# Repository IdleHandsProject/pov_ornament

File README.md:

# Persistence of Vision Christmas Ornament
A Persistence of Vision Christmas Ornament 

## Check out the video! - Click the Image

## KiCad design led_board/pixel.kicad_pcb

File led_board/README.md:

# ESPEverywhere
ESP8266 Special Make/100 Kickstarter Edition

Check out why this board exists here:
https://www.youtube.com/watch?v=67Kh_ikb-ds

The ESP Everywhere was made to take part in the Kickstarter Make/100 Campaign
You can get 1 of 100 boards assembled by me. Or you can Make your own.
Kickstarter is here:
https://www.kickstarter.com/projects/idlehandsdev/esp-everywhere-kickstarter-special-make-100

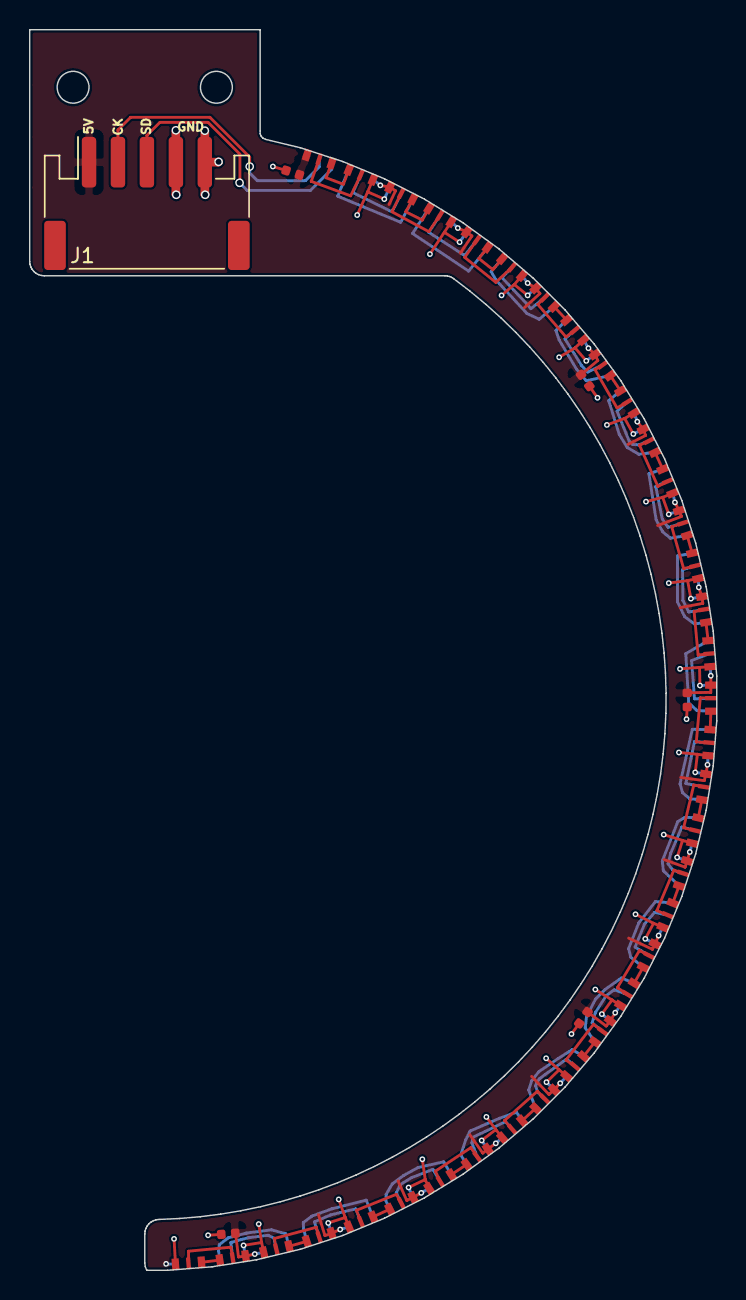
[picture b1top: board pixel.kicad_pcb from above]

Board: 2 copper layers, 47.5 x 85.7 mm, 42 parts (0 on the bottom side), 74 nets.

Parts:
C1, C10: e; C_0402_1005Metric
C3, C6, C7: 10uF; C_0402_1005Metric
J1: LED_Conn; JST_PH_S5B-PH-SM4-TB_1x05-1MP_P2.00mm_Horizontal
U1, U3, U5, U7, U9, U11, U13, U15, U17, U19, U21, U23, U25, U27, U29, U31, U33, U35: APA102; LED-APA102-2020_Edge
U2, U4, U6, U8, U10, U12, U14, U16, U18, U20, U22, U24, U26, U28, U30, U32, U34, U36: APA102; LED-APA102-2020_Edge_R

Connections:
+5V: C1.1, C3.1, C6.1, C7.1, C10.1, J1.1, U1.1, U2.1, U3.1, U4.1, U5.1, U6.1, U7.1, U8.1, U9.1, U10.1, U11.1, U12.1, U13.1, U14.1, U15.1, U16.1, U17.1, U18.1, U19.1, U20.1, U21.1, U22.1, U23.1, U24.1, U25.1, U26.1, U27.1, U28.1, U29.1, U30.1, U31.1, U32.1, U33.1, U34.1, U35.1, U36.1
CK1: U16.2, U17.5
CK2: U32.2, U33.5
CKS: J1.2, U1.5
GND: C1.2, C3.2, C6.2, C7.2, C10.2, J1.4, J1.5, U1.6, U2.6, U3.6, U4.6, U5.6, U6.6, U7.6, U8.6, U9.6, U10.6, U11.6, U12.6, U13.6, U14.6, U15.6, U16.6, U17.6, U18.6, U19.6, U20.6, U21.6, U22.6, U23.6, U24.6, U25.6, U26.6, U27.6, U28.6, U29.6, U30.6, U31.6, U32.6, U33.6, U34.6, U35.6, U36.6
unnamed: U1.2, U2.5
unnamed: U1.3, U2.4
unnamed: U2.2, U3.5
unnamed: U2.3, U3.4
unnamed: U3.2, U4.5
unnamed: U3.3, U4.4
unnamed: U4.2, U5.5
unnamed: U4.3, U5.4
unnamed: U5.2, U6.5
unnamed: U5.3, U6.4
unnamed: U6.2, U7.5
unnamed: U6.3, U7.4
unnamed: U7.2, U8.5
unnamed: U7.3, U8.4
unnamed: U8.2, U9.5
unnamed: U8.3, U9.4
unnamed: U10.2, U11.5
unnamed: U10.3, U11.4
unnamed: U9.3, U10.4
unnamed: U9.2, U10.5
unnamed: U11.2, U12.5
unnamed: U11.3, U12.4
unnamed: U12.2, U13.5
unnamed: U12.3, U13.4
unnamed: U13.2, U14.5
unnamed: U13.3, U14.4
unnamed: U14.2, U15.5
unnamed: U14.3, U15.4
unnamed: U15.2, U16.5
unnamed: U15.3, U16.4
unnamed: U17.2, U18.5
unnamed: U17.3, U18.4
unnamed: U18.2, U19.5
unnamed: U18.3, U19.4
unnamed: U19.2, U20.5
unnamed: U19.3, U20.4
unnamed: U20.2, U21.5
unnamed: U20.3, U21.4
unnamed: U21.2, U22.5
unnamed: U21.3, U22.4
unnamed: U22.2, U23.5
unnamed: U22.3, U23.4
unnamed: U23.2, U24.5
unnamed: U23.3, U24.4
unnamed: U24.2, U25.5
unnamed: U24.3, U25.4
unnamed: U25.2, U26.5
unnamed: U25.3, U26.4
unnamed: U26.2, U27.5
unnamed: U26.3, U27.4
unnamed: U27.2, U28.5
unnamed: U27.3, U28.4
unnamed: U28.2, U29.5
unnamed: U28.3, U29.4
unnamed: U29.2, U30.5
unnamed: U29.3, U30.4
unnamed: U30.2, U31.5
unnamed: U30.3, U31.4
unnamed: U31.2, U32.5
unnamed: U31.3, U32.4
unnamed: U33.2, U34.5
unnamed: U33.3, U34.4
unnamed: U34.2, U35.5
unnamed: U34.3, U35.4
unnamed: U35.2, U36.5
unnamed: U35.3, U36.4
SD1: U16.3, U17.4
SD2: U32.3, U33.4
SDS: J1.3, U1.4

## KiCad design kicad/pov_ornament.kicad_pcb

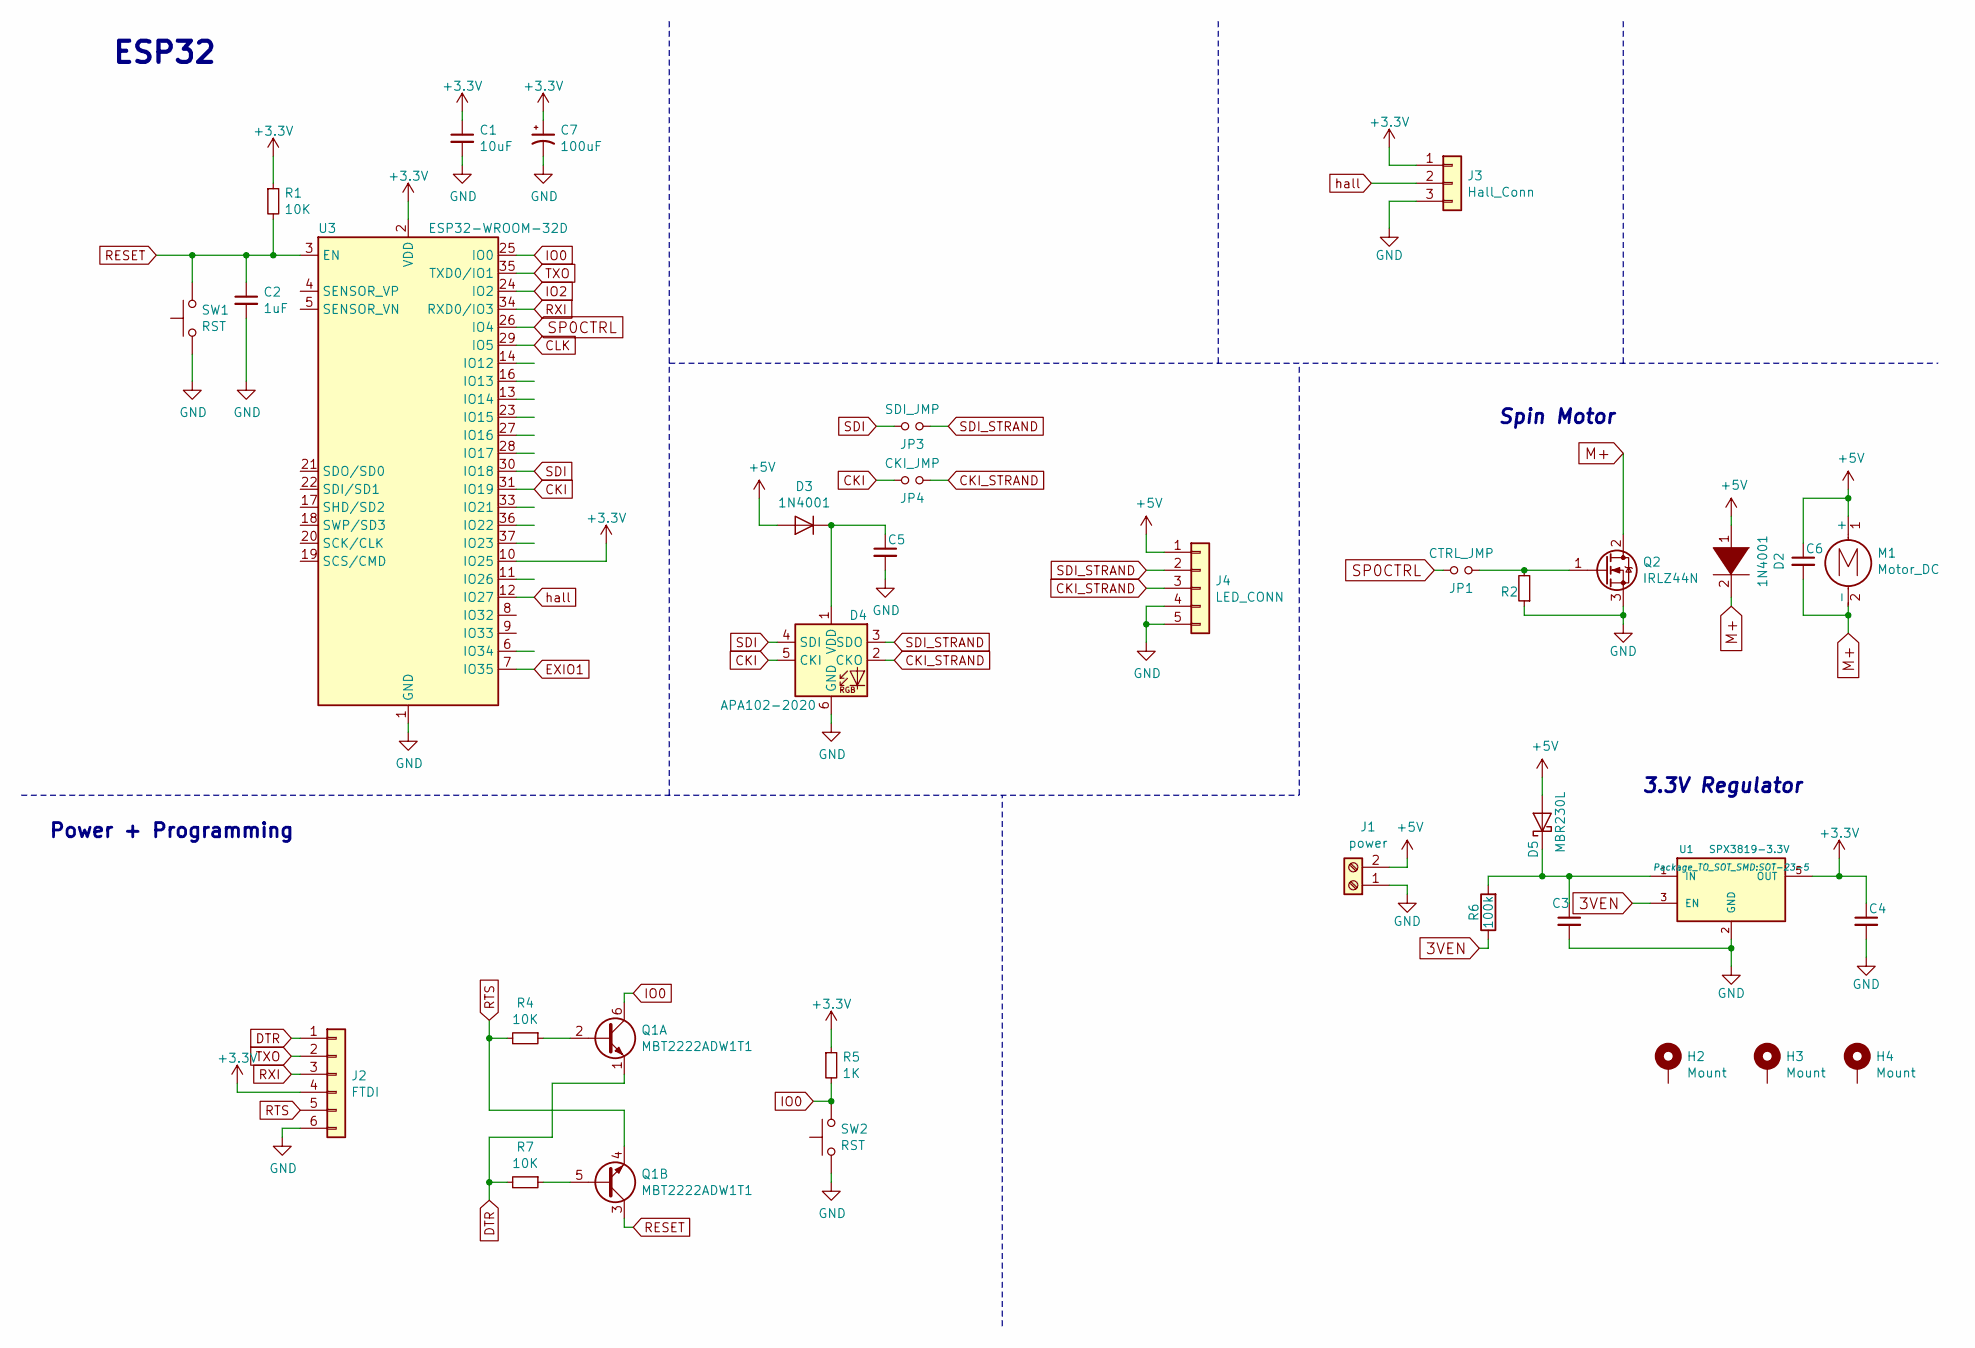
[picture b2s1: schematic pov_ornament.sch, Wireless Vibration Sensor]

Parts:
C1: 10uF; C_0805_2012Metric; Digikey Part No. 490-10516-2-ND
C2, C3: 1uF; C_0805_2012Metric; Digikey Part No. 1276-1066-2-ND
C4, C5: 2.2uF; C_0805_2012Metric; Digikey Part No. 311-1870-2-ND
C6: 100pF; C_0805_2012Metric; Digikey Part No. 311-1870-2-ND
C7: 100uF; CP_Elec_6.3x4.5; Digikey Part No. 399-6726-2-ND
D2, D3: 1N4001; D_DO-41_SOD81_P7.62mm_Horizontal; Digikey Part No. 1N4001-TPMSCT-ND
D4: APA102-2020; LED-APA102-2020_no_center; Digikey Part No. 1528-1826-ND
D5: MBR230L; D_SOD-123F; Digikey Part No. MBR230LSFT1GOSCT-ND
H2, H3, H4: Mount; MountingHole_3.5mm_Pad
J1: power; TerminalBlock_Phoenix_MKDS-3-2-5.08_1x02_P5.08mm_Horizontal
J2: FTDI; PinHeader_1x06_P2.54mm_Vertical; Digikey Part No. 2057-PH1-06-UA-ND
J3: Hall_Conn; JST_PH_B3B-PH-K_1x03_P2.00mm_Vertical; Digikey Part No. 455-1705-ND
J4: LED_CONN; JST_PH_B5B-PH-K_1x05_P2.00mm_Vertical; Digikey Part No. 455-1707-ND
JP1: CTRL_JMP; PinHeader_1x02_P2.54mm_Vertical
JP3: SDI_JMP; PinHeader_1x02_P2.54mm_Vertical
JP4: CKI_JMP; PinHeader_1x02_P2.54mm_Vertical
M1: Motor_DC; Microgeared_motor_pololu
Q1: MBT2222ADW1T1; SOT-363_SC-70-6; Digikey Part No. MBT2222ADW1T1GOSTR-ND
Q2: IRLZ44N; TO-263-2; Digikey Part No. IRLZ44NSTRLPBFTR-ND
R1, R2, R4, R7: 10K; R_0805_2012Metric; Digikey Part No. 311-10KARTR-ND
R5: 1K; R_0805_2012Metric; Digikey Part No. 311-1KARTR-ND
R6: 100k; R_0805_2012Metric; Digikey Part No. ‎311-100KCRCT-ND‎
SW1, SW2: RST; SW_SPST_CK_RS282G05A3; Digikey Part No. CKN10384TR-ND
U1: SPX3819-3.3V; SOT-23-5; Digikey Part No. 1016-1873-1-ND
U3: ESP32-WROOM-32D; ESP32-WROOM-32; Digikey Part No. 1904-1023-2-ND

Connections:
3VEN: R6.1, U1.3 (EN)
+3V3: C1.1, C4.1, C7.1, J2.4, J3.1, R1.1, R5.1, U1.5 (OUT), U3.2 (VDD), U3.10 (IO25)
+5V: C6.1, D2.1 (K), D3.2 (A), D5.2 (A), J1.2, J4.1, M1.1 (+)
CKI: D4.5 (CKI), JP4.1, U3.31 (IO19)
CKI_STRAND: D4.2 (CKO), J4.3, JP4.2
CLK: U3.29 (IO5)
DTR: J2.1, Q1.1 (E1), R7.2
EXIO1: U3.7 (IO35)
GND: C1.2, C2.2, C3.2, C4.2, C5.2, C7.2, D4.6 (GND), J1.1, J2.6, J3.3, J4.4, J4.5, Q2.3 (S), R2.1, SW1.1, SW2.1, U1.2 (GND), U3.1 (GND), U3.15 (GND), U3.38 (GND), U3.39 (GND)
IO0: Q1.6 (C1), R5.2, SW2.2, U3.25 (IO0)
IO2: U3.24 (IO2)
M+: C6.2, D2.2 (A), M1.2 (-), Q2.2 (D)
unnamed: C3.1, D5.1 (K), R6.2, U1.1 (IN)
unnamed: C5.1, D3.1 (K), D4.1 (VDD)
unnamed: JP1.2, Q2.1 (G), R2.2
unnamed: Q1.2 (B1), R4.1
unnamed: Q1.5 (B2), R7.1
RESET: C2.1, Q1.3 (C2), R1.2, SW1.2, U3.3 (EN)
RTS: J2.5, Q1.4 (E2), R4.2
RXI: J2.3, U3.34 (RXD0/IO3)
SDI: D4.4 (SDI), JP3.1, U3.30 (IO18)
SDI_STRAND: D4.3 (SDO), J4.2, JP3.2
SP0CTRL: JP1.1, U3.26 (IO4)
TXO: J2.2, U3.35 (TXD0/IO1)
hall: J3.2, U3.12 (IO27)

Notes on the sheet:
ESP32
Power + Programming
Spin Motor
3.3V Regulator

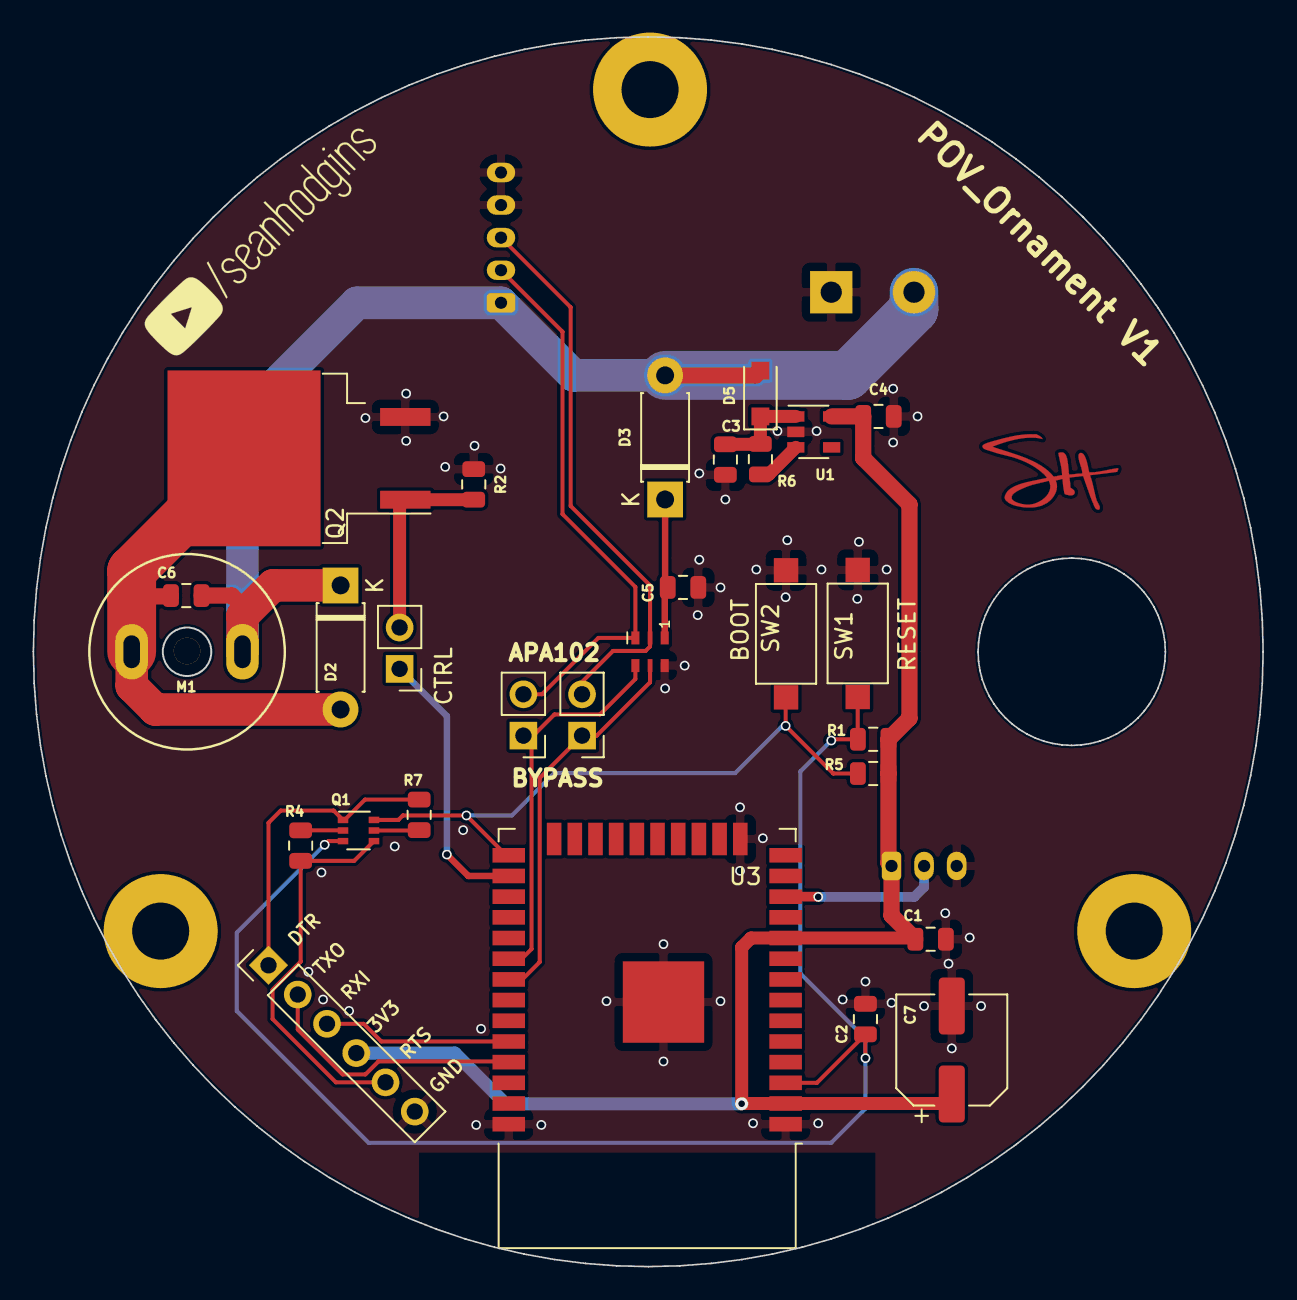
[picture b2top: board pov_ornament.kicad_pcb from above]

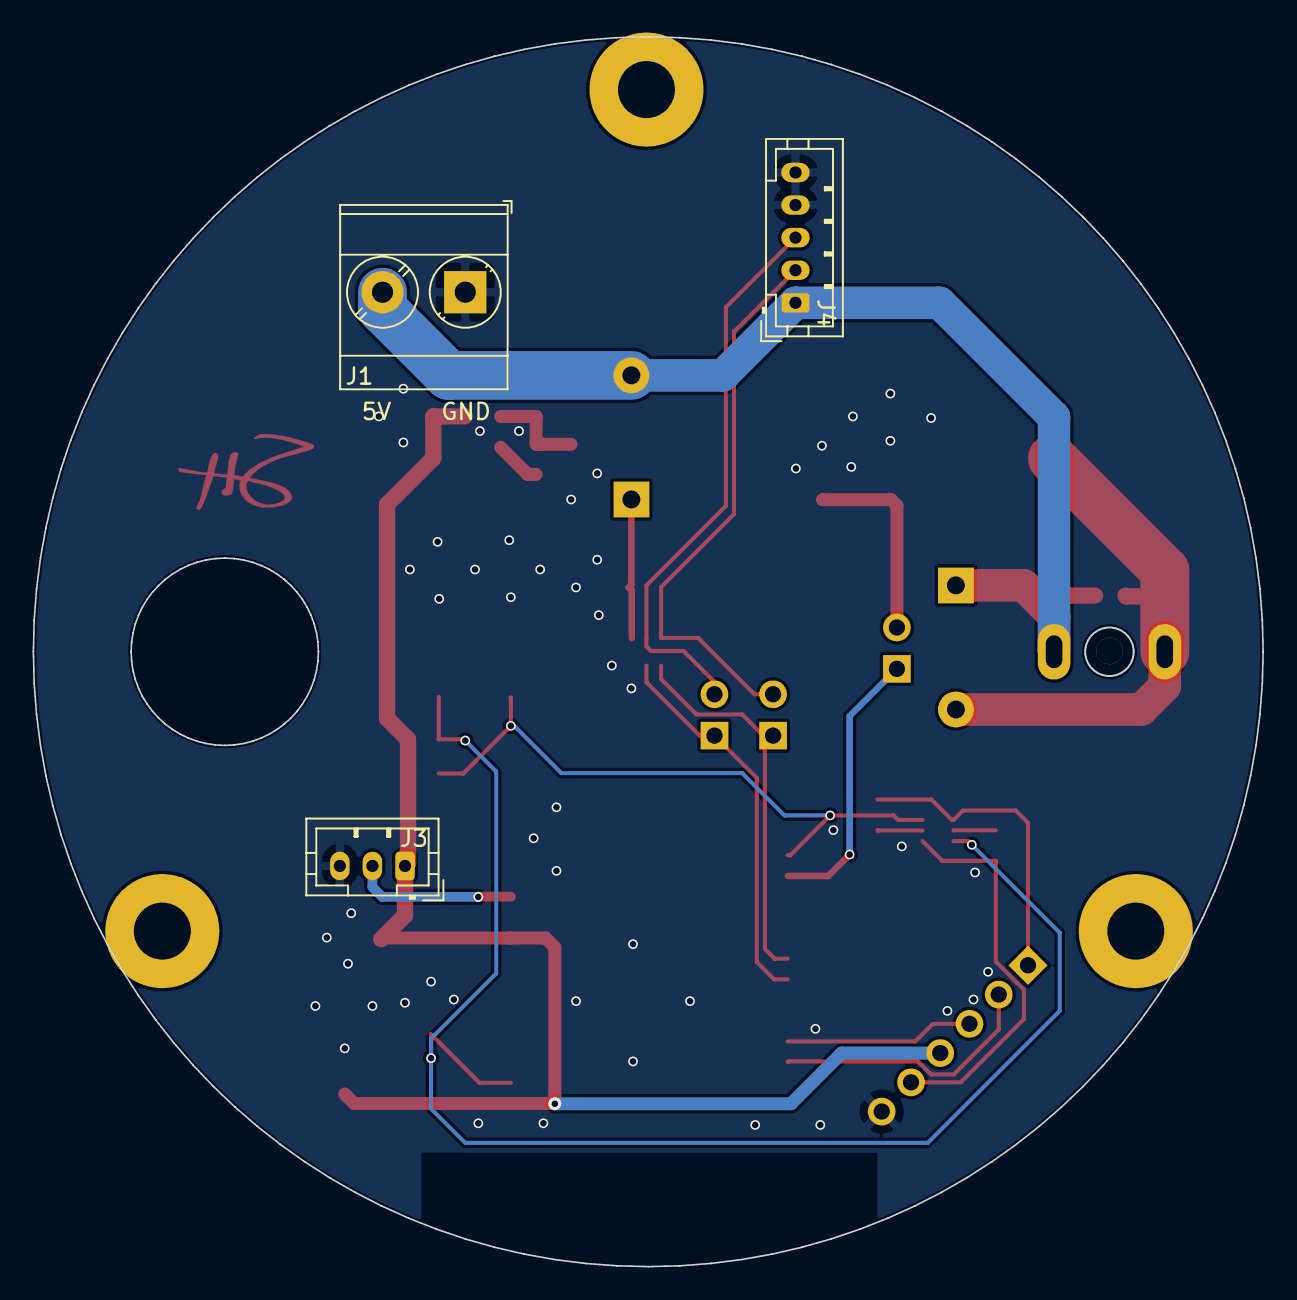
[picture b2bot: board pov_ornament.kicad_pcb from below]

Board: 2 copper layers, 75.5 x 75.5 mm, 34 parts (3 on the bottom side), 22 nets.

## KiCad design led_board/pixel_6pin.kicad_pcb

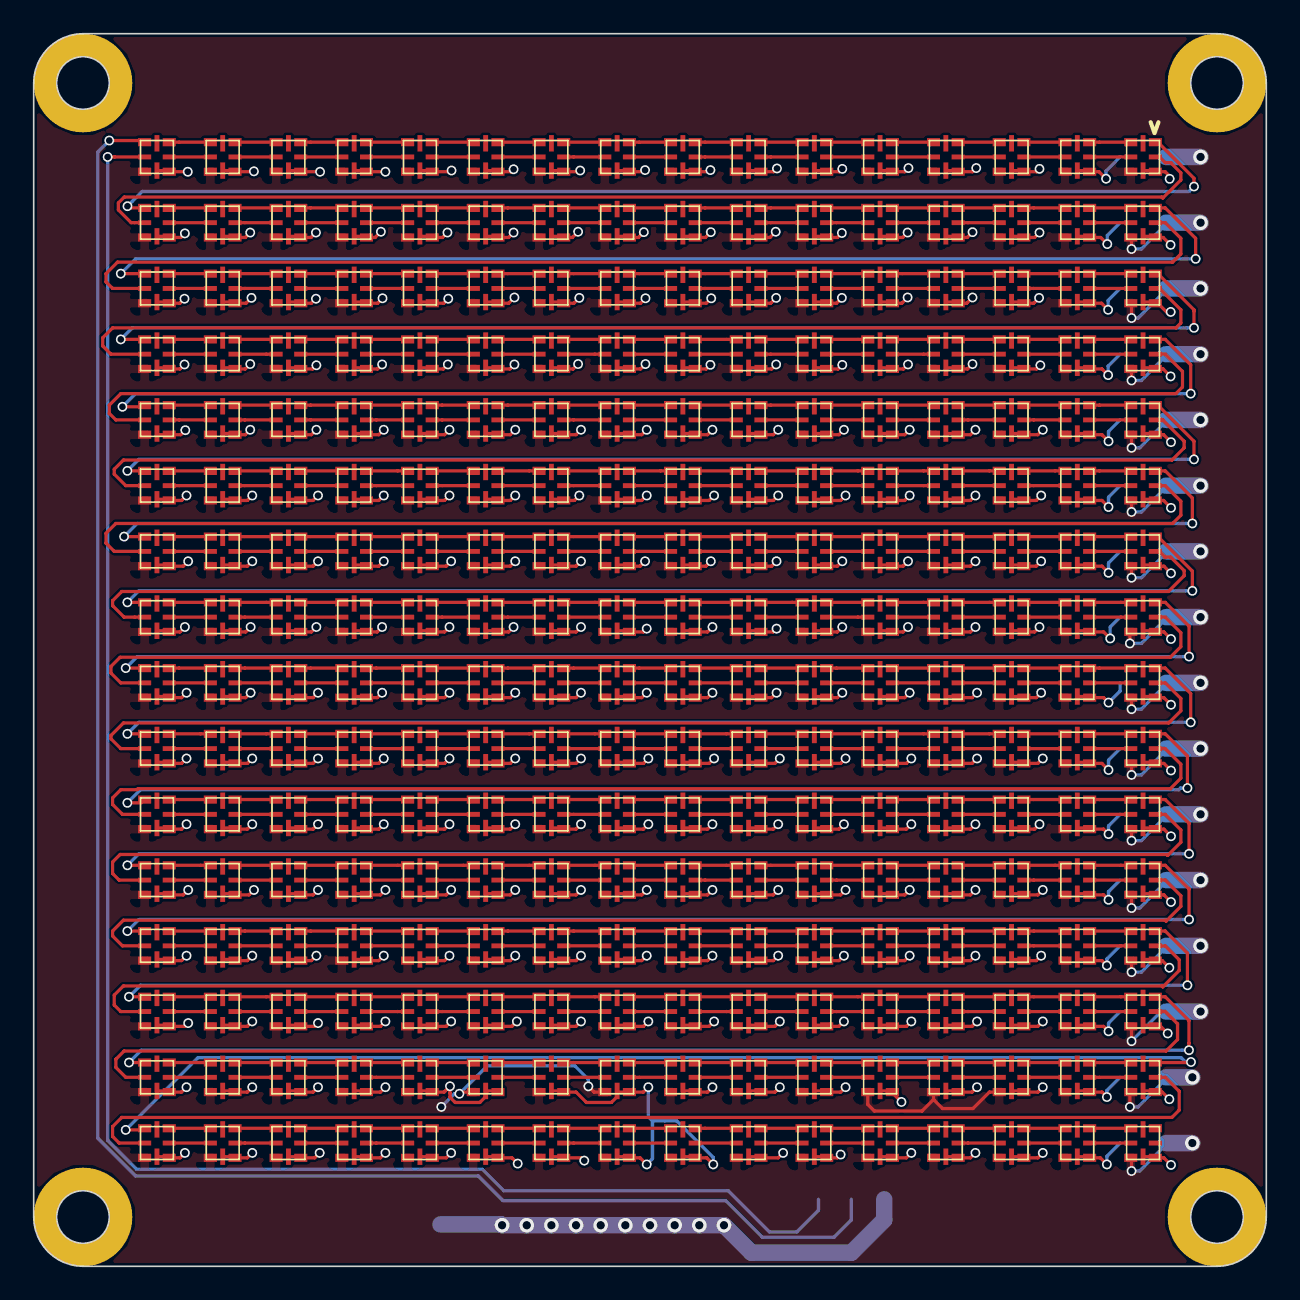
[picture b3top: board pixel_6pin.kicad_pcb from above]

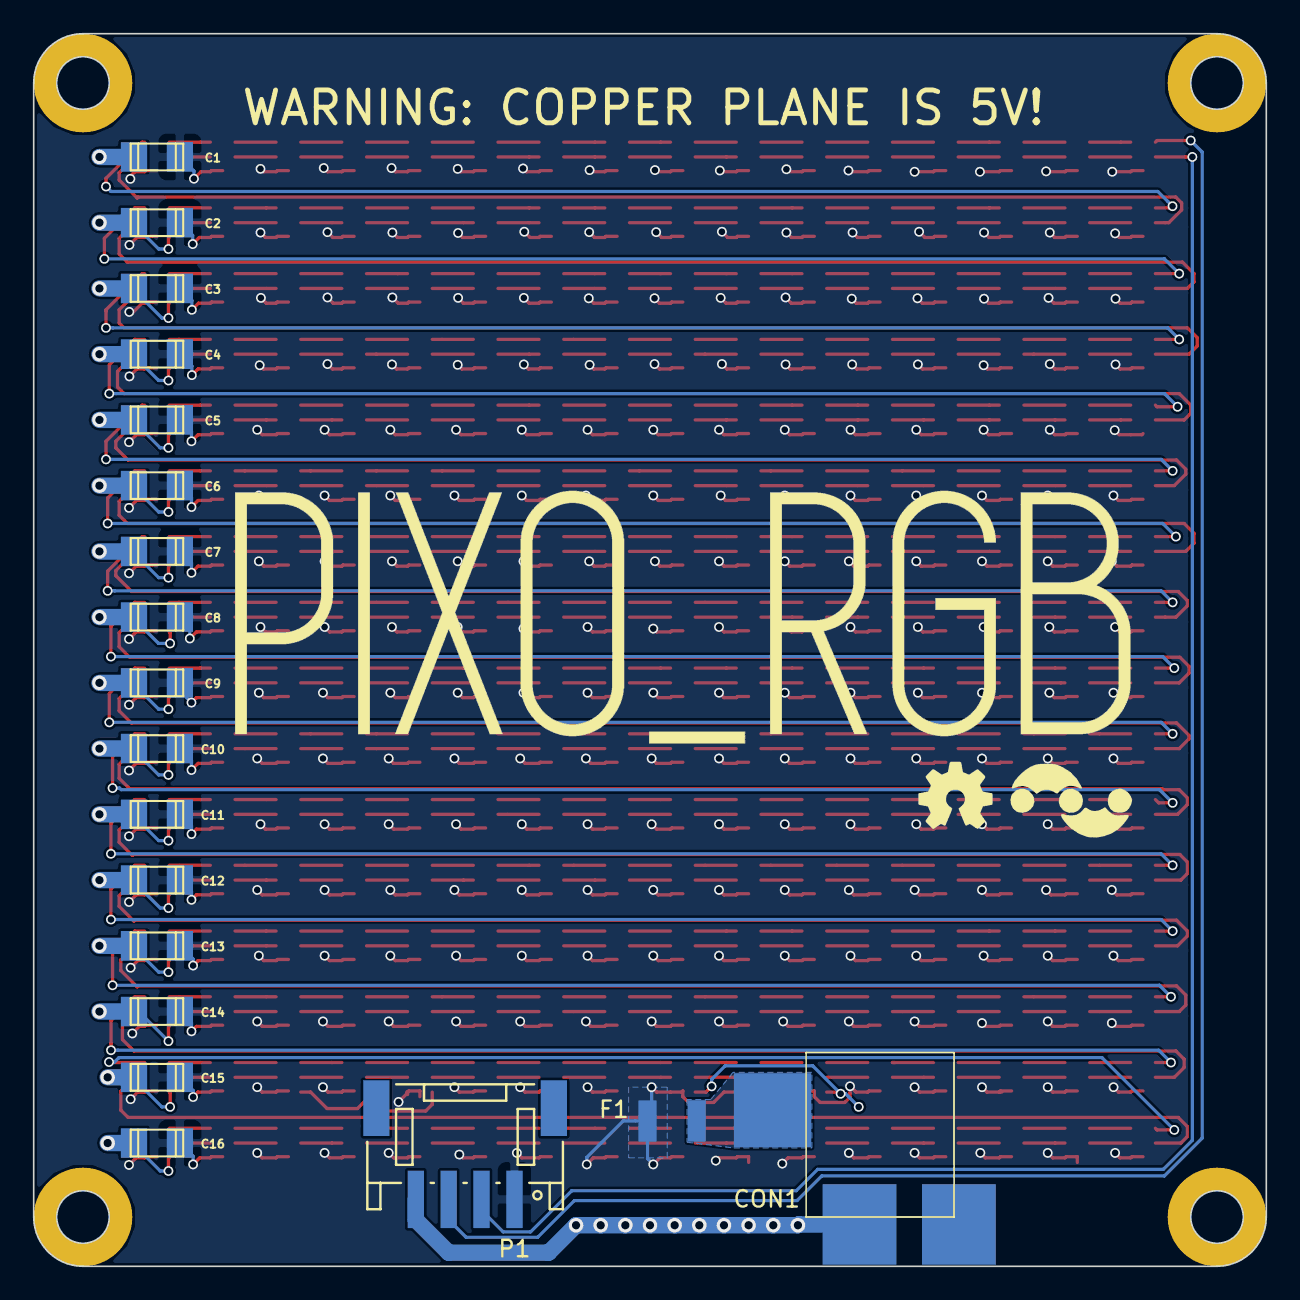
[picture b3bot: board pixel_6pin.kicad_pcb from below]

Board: 2 copper layers, 75.0 x 75.0 mm, 275 parts (19 on the bottom side), 515 nets.

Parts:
C1, C2, C3, C4, C5, C6, C7, C8, C9, C10, C11, C12, C13, C14, C15, C16: 10uF; c_1206
CON1: BARREL_JACK; DC_POWERJACK_VERT_NoHoles
F1: 5A_Hold; Fuse_SMD1210_Reflow
P1: CONN_01X04; Connectors_JST_S4B-PH-SM4-TB
U1, U2, U3, U4, U5, U6, U7, U8, U9, U10, U11, U12, U13, U14, U15, U16, U17, U18, U19, U20, U21, U22, U23, U24, U25, U26, U27, U28, U29, U30, U31, U32, U33, U34, U35, U36, U37, U38, U39, U40, U41, U42, U43, U44, U45, U46, U47, U48, U49, U50, U51, U52, U53, U54, U55, U56, U57, U58, U59, U60, U61, U62, U63, U64, U65, U66, U67, U68, U69, U70, U71, U72, U73, U74, U75, U76, U77, U78, U79, U80, U81, U82, U83, U84, U85, U86, U87, U88, U89, U90, U91, U92, U93, U94, U95, U96, U97, U98, U99, U100, U101, U102, U103, U104, U105, U106, U107, U108, U109, U110, U111, U112, U113, U114, U115, U116, U117, U118, U119, U120, U121, U122, U123, U124, U125, U126, U127, U128, U129, U130, U131, U132, U133, U134, U135, U136, U137, U138, U139, U140, U141, U142, U143, U144, U145, U146, U147, U148, U149, U150, U151, U152, U153, U154, U155, U156, U157, U158, U159, U160, U161, U162, U163, U164, U165, U166, U167, U168, U169, U170, U171, U172, U173, U174, U175, U176, U177, U178, U179, U180, U181, U182, U183, U184, U185, U186, U187, U188, U189, U190, U191, U192, U193, U194, U195, U196, U197, U198, U199, U200, U201, U202, U203, U204, U205, U206, U207, U208, U209, U210, U211, U212, U213, U214, U215, U216, U217, U218, U219, U220, U221, U222, U223, U224, U225, U226, U227, U228, U229, U230, U231, U232, U233, U234, U235, U236, U237, U238, U239, U240, U241, U242, U243, U244, U245, U246, U247, U248, U249, U250, U251, U252, U253, U254, U255, U256: APA102; APA102-2020_NOGND

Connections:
+5V: C1.1, C2.1, C3.1, C4.1, C5.1, C6.1, C7.1, C8.1, C9.1, C10.1, C11.1, C12.1, C13.1, C14.1, C15.1, C16.1, F1.1, P1.1, U1.1, U2.1, U3.1, U4.1, U5.1, U6.1, U7.1, U8.1, U9.1, U10.1, U11.1, U12.1, U13.1, U14.1, U15.1, U16.1, U17.1, U18.1, U19.1, U20.1, U21.1, U22.1, U23.1, U24.1, U25.1, U26.1, U27.1, U28.1, U29.1, U30.1, U31.1, U32.1, U33.1, U34.1, U35.1, U36.1, U37.1, U38.1, U39.1, U40.1, U41.1, U42.1, U43.1, U44.1, U45.1, U46.1, U47.1, U48.1, U49.1, U50.1, U51.1, U52.1, U53.1, U54.1, U55.1, U56.1, U57.1, U58.1, U59.1, U60.1, U61.1, U62.1, U63.1, U64.1, U65.1, U66.1, U67.1, U68.1, U69.1, U70.1, U71.1, U72.1, U73.1, U74.1, U75.1, U76.1, U77.1, U78.1, U79.1, U80.1, U81.1, U82.1, U83.1, U84.1, U85.1, U86.1, U87.1, U88.1, U89.1, U90.1, U91.1, U92.1, U93.1, U94.1, U95.1, U96.1, U97.1, U98.1, U99.1, U100.1, U101.1, U102.1, U103.1, U104.1, U105.1, U106.1, U107.1, U108.1, U109.1, U110.1, U111.1, U112.1, U113.1, U114.1, U115.1, U116.1, U117.1, U118.1, U119.1, U120.1, U121.1, U122.1, U123.1, U124.1, U125.1, U126.1, U127.1, U128.1, U129.1, U130.1, U131.1, U132.1, U133.1, U134.1, U135.1, U136.1, U137.1, U138.1, U139.1, U140.1, U141.1, U142.1, U143.1, U144.1, U145.1, U146.1, U147.1, U148.1, U149.1, U150.1, U151.1, U152.1, U153.1, U154.1, U155.1, U156.1, U157.1, U158.1, U159.1, U160.1, U161.1, U162.1, U163.1, U164.1, U165.1, U166.1, U167.1, U168.1, U169.1, U170.1, U171.1, U172.1, U173.1, U174.1, U175.1, U176.1, U177.1, U178.1, U179.1, U180.1, U181.1, U182.1, U183.1, U184.1, U185.1, U186.1, U187.1, U188.1, U189.1, U190.1, U191.1, U192.1, U193.1, U194.1, U195.1, U196.1, U197.1, U198.1, U199.1, U200.1, U201.1, U202.1, U203.1, U204.1, U205.1, U206.1, U207.1, U208.1, U209.1, U210.1, U211.1, U212.1, U213.1, U214.1, U215.1, U216.1, U217.1, U218.1, U219.1, U220.1, U221.1, U222.1, U223.1, U224.1, U225.1, U226.1, U227.1, U228.1, U229.1, U230.1, U231.1, U232.1, U233.1, U234.1, U235.1, U236.1, U237.1, U238.1, U239.1, U240.1, U241.1, U242.1, U243.1, U244.1, U245.1, U246.1, U247.1, U248.1, U249.1, U250.1, U251.1, U252.1, U253.1, U254.1, U255.1, U256.1
CK1: U16.2, U17.5
CK2: U32.2, U33.5
CK3: U48.2, U49.5
CK4: U64.2, U65.5
CK5: U80.2, U81.5
CK6: U96.2, U97.5
CK7: U112.2, U113.5
CK8: U128.2, U129.5
CK9: U144.2, U145.5
CK10: U160.2, U161.5
CK11: U176.2, U177.5
CK12: U192.2, U193.5
CK13: U208.2, U209.5
CK14: U224.2, U225.5
CK15: U240.2, U241.5
CKS: P1.2, U1.5
GND: C1.2, C2.2, C3.2, C4.2, C5.2, C6.2, C7.2, C8.2, C9.2, C10.2, C11.2, C12.2, C13.2, C14.2, C15.2, C16.2, CON1.2, P1.4, U1.6, U2.6, U3.6, U4.6, U5.6, U6.6, U7.6, U8.6, U9.6, U10.6, U11.6, U12.6, U13.6, U14.6, U15.6, U16.6, U17.6, U18.6, U19.6, U20.6, U21.6, U22.6, U23.6, U24.6, U25.6, U26.6, U27.6, U28.6, U29.6, U30.6, U31.6, U32.6, U33.6, U34.6, U35.6, U36.6, U37.6, U38.6, U39.6, U40.6, U41.6, U42.6, U43.6, U44.6, U45.6, U46.6, U47.6, U48.6, U49.6, U50.6, U51.6, U52.6, U53.6, U54.6, U55.6, U56.6, U57.6, U58.6, U59.6, U60.6, U61.6, U62.6, U63.6, U64.6, U65.6, U66.6, U67.6, U68.6, U69.6, U70.6, U71.6, U72.6, U73.6, U74.6, U75.6, U76.6, U77.6, U78.6, U79.6, U80.6, U81.6, U82.6, U83.6, U84.6, U85.6, U86.6, U87.6, U88.6, U89.6, U90.6, U91.6, U92.6, U93.6, U94.6, U95.6, U96.6, U97.6, U98.6, U99.6, U100.6, U101.6, U102.6, U103.6, U104.6, U105.6, U106.6, U107.6, U108.6, U109.6, U110.6, U111.6, U112.6, U113.6, U114.6, U115.6, U116.6, U117.6, U118.6, U119.6, U120.6, U121.6, U122.6, U123.6, U124.6, U125.6, U126.6, U127.6, U128.6, U129.6, U130.6, U131.6, U132.6, U133.6, U134.6, U135.6, U136.6, U137.6, U138.6, U139.6, U140.6, U141.6, U142.6, U143.6, U144.6, U145.6, U146.6, U147.6, U148.6, U149.6, U150.6, U151.6, U152.6, U153.6, U154.6, U155.6, U156.6, U157.6, U158.6, U159.6, U160.6, U161.6, U162.6, U163.6, U164.6, U165.6, U166.6, U167.6, U168.6, U169.6, U170.6, U171.6, U172.6, U173.6, U174.6, U175.6, U176.6, U177.6, U178.6, U179.6, U180.6, U181.6, U182.6, U183.6, U184.6, U185.6, U186.6, U187.6, U188.6, U189.6, U190.6, U191.6, U192.6, U193.6, U194.6, U195.6, U196.6, U197.6, U198.6, U199.6, U200.6, U201.6, U202.6, U203.6, U204.6, U205.6, U206.6, U207.6, U208.6, U209.6, U210.6, U211.6, U212.6, U213.6, U214.6, U215.6, U216.6, U217.6, U218.6, U219.6, U220.6, U221.6, U222.6, U223.6, U224.6, U225.6, U226.6, U227.6, U228.6, U229.6, U230.6, U231.6, U232.6, U233.6, U234.6, U235.6, U236.6, U237.6, U238.6, U239.6, U240.6, U241.6, U242.6, U243.6, U244.6, U245.6, U246.6, U247.6, U248.6, U249.6, U250.6, U251.6, U252.6, U253.6, U254.6, U255.6, U256.6
unnamed: CON1.1, F1.2
unnamed: U1.2, U2.5
unnamed: U1.3, U2.4
unnamed: U2.2, U3.5
unnamed: U2.3, U3.4
unnamed: U3.2, U4.5
unnamed: U3.3, U4.4
unnamed: U4.2, U5.5
unnamed: U4.3, U5.4
unnamed: U5.2, U6.5
unnamed: U5.3, U6.4
unnamed: U6.2, U7.5
unnamed: U6.3, U7.4
unnamed: U7.2, U8.5
unnamed: U7.3, U8.4
unnamed: U8.2, U9.5
unnamed: U8.3, U9.4
unnamed: U10.2, U11.5
unnamed: U10.3, U11.4
unnamed: U9.3, U10.4
unnamed: U9.2, U10.5
unnamed: U11.2, U12.5
unnamed: U11.3, U12.4
unnamed: U12.2, U13.5
unnamed: U12.3, U13.4
unnamed: U13.2, U14.5
unnamed: U13.3, U14.4
unnamed: U14.2, U15.5
unnamed: U14.3, U15.4
unnamed: U15.2, U16.5
unnamed: U15.3, U16.4
unnamed: U17.2, U18.5
unnamed: U17.3, U18.4
unnamed: U18.2, U19.5
unnamed: U18.3, U19.4
unnamed: U19.2, U20.5
unnamed: U19.3, U20.4
unnamed: U20.2, U21.5
unnamed: U20.3, U21.4
unnamed: U21.2, U22.5
unnamed: U21.3, U22.4
unnamed: U22.2, U23.5
unnamed: U22.3, U23.4
unnamed: U23.2, U24.5
unnamed: U23.3, U24.4
unnamed: U24.2, U25.5
unnamed: U24.3, U25.4
unnamed: U25.2, U26.5
unnamed: U25.3, U26.4
unnamed: U26.2, U27.5
unnamed: U26.3, U27.4
unnamed: U27.2, U28.5
unnamed: U27.3, U28.4
unnamed: U28.2, U29.5
unnamed: U28.3, U29.4
unnamed: U29.2, U30.5
unnamed: U29.3, U30.4
unnamed: U30.2, U31.5
unnamed: U30.3, U31.4
unnamed: U31.2, U32.5
unnamed: U31.3, U32.4
unnamed: U33.2, U34.5
unnamed: U33.3, U34.4
unnamed: U34.2, U35.5
unnamed: U34.3, U35.4
unnamed: U35.2, U36.5
unnamed: U35.3, U36.4
unnamed: U36.2, U37.5
unnamed: U36.3, U37.4
unnamed: U37.2, U38.5
unnamed: U37.3, U38.4
unnamed: U38.2, U39.5
unnamed: U38.3, U39.4
unnamed: U39.2, U40.5
unnamed: U39.3, U40.4
unnamed: U40.2, U41.5
unnamed: U40.3, U41.4
unnamed: U41.2, U42.5
unnamed: U41.3, U42.4
unnamed: U42.2, U43.5
unnamed: U42.3, U43.4
unnamed: U43.2, U44.5
unnamed: U43.3, U44.4
unnamed: U44.2, U45.5
unnamed: U44.3, U45.4
unnamed: U45.2, U46.5
unnamed: U45.3, U46.4
unnamed: U46.2, U47.5
unnamed: U46.3, U47.4
unnamed: U47.2, U48.5
unnamed: U47.3, U48.4
unnamed: U49.2, U50.5
unnamed: U49.3, U50.4
unnamed: U50.2, U51.5
unnamed: U50.3, U51.4
unnamed: U51.2, U52.5
unnamed: U51.3, U52.4
unnamed: U52.2, U53.5
unnamed: U52.3, U53.4
unnamed: U53.2, U54.5
unnamed: U53.3, U54.4
unnamed: U54.2, U55.5
unnamed: U54.3, U55.4
unnamed: U55.2, U56.5
unnamed: U55.3, U56.4
unnamed: U56.2, U57.5
unnamed: U56.3, U57.4
unnamed: U57.2, U58.5
unnamed: U57.3, U58.4
unnamed: U58.2, U59.5
unnamed: U58.3, U59.4
unnamed: U59.2, U60.5
unnamed: U59.3, U60.4
unnamed: U60.2, U61.5
unnamed: U60.3, U61.4
unnamed: U61.2, U62.5
unnamed: U61.3, U62.4
unnamed: U62.2, U63.5
unnamed: U62.3, U63.4
unnamed: U63.2, U64.5
unnamed: U63.3, U64.4
unnamed: U65.2, U66.5
unnamed: U65.3, U66.4
unnamed: U66.2, U67.5
unnamed: U66.3, U67.4
unnamed: U67.2, U68.5
unnamed: U67.3, U68.4
unnamed: U68.2, U69.5
unnamed: U68.3, U69.4
unnamed: U69.2, U70.5
unnamed: U69.3, U70.4
unnamed: U70.2, U71.5
unnamed: U70.3, U71.4
unnamed: U71.2, U72.5
unnamed: U71.3, U72.4
unnamed: U72.2, U73.5
unnamed: U72.3, U73.4
unnamed: U73.2, U74.5
unnamed: U73.3, U74.4
unnamed: U74.2, U75.5
unnamed: U74.3, U75.4
unnamed: U75.2, U76.5
unnamed: U75.3, U76.4
unnamed: U76.2, U77.5
unnamed: U76.3, U77.4
unnamed: U77.2, U78.5
unnamed: U77.3, U78.4
unnamed: U78.2, U79.5
unnamed: U78.3, U79.4
unnamed: U79.2, U80.5
unnamed: U79.3, U80.4
unnamed: U81.2, U82.5
unnamed: U81.3, U82.4
unnamed: U82.2, U83.5
unnamed: U82.3, U83.4
unnamed: U83.2, U84.5
unnamed: U83.3, U84.4
unnamed: U84.2, U85.5
unnamed: U84.3, U85.4
unnamed: U85.2, U86.5
unnamed: U85.3, U86.4
unnamed: U86.2, U87.5
unnamed: U86.3, U87.4
unnamed: U87.2, U88.5
unnamed: U87.3, U88.4
unnamed: U88.2, U89.5
unnamed: U88.3, U89.4
unnamed: U89.2, U90.5
unnamed: U89.3, U90.4
unnamed: U90.2, U91.5
unnamed: U90.3, U91.4
unnamed: U91.2, U92.5
unnamed: U91.3, U92.4
unnamed: U92.2, U93.5
unnamed: U92.3, U93.4
unnamed: U93.2, U94.5
unnamed: U93.3, U94.4
unnamed: U94.2, U95.5
unnamed: U94.3, U95.4
unnamed: U95.2, U96.5
unnamed: U95.3, U96.4
unnamed: U97.2, U98.5
unnamed: U97.3, U98.4
unnamed: U98.2, U99.5
unnamed: U98.3, U99.4
unnamed: U100.2, U101.5
unnamed: U100.3, U101.4
unnamed: U99.3, U100.4
unnamed: U99.2, U100.5
unnamed: U101.2, U102.5
unnamed: U101.3, U102.4
unnamed: U102.2, U103.5
unnamed: U102.3, U103.4
unnamed: U103.2, U104.5
unnamed: U103.3, U104.4
unnamed: U104.2, U105.5
unnamed: U104.3, U105.4
unnamed: U105.2, U106.5
unnamed: U105.3, U106.4
unnamed: U106.2, U107.5
unnamed: U106.3, U107.4
unnamed: U107.2, U108.5
unnamed: U107.3, U108.4
unnamed: U108.2, U109.5
unnamed: U108.3, U109.4
unnamed: U109.2, U110.5
unnamed: U109.3, U110.4
unnamed: U110.2, U111.5
unnamed: U110.3, U111.4
unnamed: U111.2, U112.5
unnamed: U111.3, U112.4
unnamed: U113.2, U114.5
unnamed: U113.3, U114.4
unnamed: U114.2, U115.5
unnamed: U114.3, U115.4
unnamed: U115.2, U116.5
unnamed: U115.3, U116.4
unnamed: U116.2, U117.5
unnamed: U116.3, U117.4
unnamed: U117.2, U118.5
unnamed: U117.3, U118.4
unnamed: U118.2, U119.5
unnamed: U118.3, U119.4
unnamed: U119.2, U120.5
unnamed: U119.3, U120.4
unnamed: U120.2, U121.5
unnamed: U120.3, U121.4
unnamed: U121.2, U122.5
unnamed: U121.3, U122.4
unnamed: U122.2, U123.5
unnamed: U122.3, U123.4
unnamed: U123.2, U124.5
unnamed: U123.3, U124.4
unnamed: U124.2, U125.5
unnamed: U124.3, U125.4
unnamed: U125.2, U126.5
unnamed: U125.3, U126.4
unnamed: U126.2, U127.5
unnamed: U126.3, U127.4
unnamed: U127.2, U128.5
unnamed: U127.3, U128.4
unnamed: U129.2, U130.5
unnamed: U129.3, U130.4
unnamed: U130.2, U131.5
unnamed: U130.3, U131.4
unnamed: U131.2, U132.5
unnamed: U131.3, U132.4
unnamed: U132.2, U133.5
unnamed: U132.3, U133.4
unnamed: U133.2, U134.5
unnamed: U133.3, U134.4
unnamed: U134.2, U135.5
unnamed: U134.3, U135.4
unnamed: U135.2, U136.5
unnamed: U135.3, U136.4
unnamed: U136.2, U137.5
unnamed: U136.3, U137.4
unnamed: U137.2, U138.5
unnamed: U137.3, U138.4
unnamed: U138.2, U139.5
unnamed: U138.3, U139.4
unnamed: U139.2, U140.5
unnamed: U139.3, U140.4
unnamed: U140.2, U141.5
unnamed: U140.3, U141.4
unnamed: U141.2, U142.5
unnamed: U141.3, U142.4
unnamed: U142.2, U143.5
unnamed: U142.3, U143.4
unnamed: U143.2, U144.5
unnamed: U143.3, U144.4
unnamed: U145.2, U146.5
unnamed: U145.3, U146.4
unnamed: U146.2, U147.5
unnamed: U146.3, U147.4
unnamed: U147.2, U148.5
unnamed: U147.3, U148.4
unnamed: U148.2, U149.5
unnamed: U148.3, U149.4
unnamed: U149.2, U150.5
unnamed: U149.3, U150.4
unnamed: U150.2, U151.5
unnamed: U150.3, U151.4
unnamed: U151.2, U152.5
unnamed: U151.3, U152.4
unnamed: U152.2, U153.5
unnamed: U152.3, U153.4
unnamed: U153.2, U154.5
unnamed: U153.3, U154.4
unnamed: U154.2, U155.5
unnamed: U154.3, U155.4
unnamed: U155.2, U156.5
unnamed: U155.3, U156.4
unnamed: U156.2, U157.5
unnamed: U156.3, U157.4
unnamed: U157.2, U158.5
unnamed: U157.3, U158.4
unnamed: U158.2, U159.5
unnamed: U158.3, U159.4
unnamed: U159.2, U160.5
unnamed: U159.3, U160.4
unnamed: U161.2, U162.5
unnamed: U161.3, U162.4
unnamed: U162.2, U163.5
unnamed: U162.3, U163.4
unnamed: U163.2, U164.5
unnamed: U163.3, U164.4
unnamed: U164.2, U165.5
unnamed: U164.3, U165.4
unnamed: U165.2, U166.5
unnamed: U165.3, U166.4
unnamed: U166.2, U167.5
unnamed: U166.3, U167.4
unnamed: U167.2, U168.5
unnamed: U167.3, U168.4
unnamed: U168.2, U169.5
unnamed: U168.3, U169.4
unnamed: U169.2, U170.5
unnamed: U169.3, U170.4
unnamed: U170.2, U171.5
unnamed: U170.3, U171.4
unnamed: U171.2, U172.5
unnamed: U171.3, U172.4
unnamed: U172.2, U173.5
unnamed: U172.3, U173.4
unnamed: U173.2, U174.5
unnamed: U173.3, U174.4
unnamed: U174.2, U175.5
unnamed: U174.3, U175.4
unnamed: U175.2, U176.5
unnamed: U175.3, U176.4
unnamed: U177.2, U178.5
unnamed: U177.3, U178.4
unnamed: U178.2, U179.5
unnamed: U178.3, U179.4
unnamed: U179.2, U180.5
unnamed: U179.3, U180.4
unnamed: U180.2, U181.5
unnamed: U180.3, U181.4
unnamed: U181.2, U182.5
unnamed: U181.3, U182.4
unnamed: U182.2, U183.5
unnamed: U182.3, U183.4
unnamed: U183.2, U184.5
unnamed: U183.3, U184.4
unnamed: U184.2, U185.5
unnamed: U184.3, U185.4
unnamed: U185.2, U186.5
unnamed: U185.3, U186.4
unnamed: U186.2, U187.5
unnamed: U186.3, U187.4
unnamed: U187.2, U188.5
unnamed: U187.3, U188.4
unnamed: U188.2, U189.5
unnamed: U188.3, U189.4
unnamed: U189.2, U190.5
unnamed: U189.3, U190.4
unnamed: U190.2, U191.5
unnamed: U190.3, U191.4
unnamed: U191.2, U192.5
unnamed: U191.3, U192.4
unnamed: U193.2, U194.5
unnamed: U193.3, U194.4
unnamed: U194.2, U195.5
unnamed: U194.3, U195.4
unnamed: U195.2, U196.5
unnamed: U195.3, U196.4
unnamed: U196.2, U197.5
unnamed: U196.3, U197.4
unnamed: U197.2, U198.5
unnamed: U197.3, U198.4
unnamed: U198.2, U199.5
unnamed: U198.3, U199.4
unnamed: U199.2, U200.5
unnamed: U199.3, U200.4
unnamed: U200.2, U201.5
unnamed: U200.3, U201.4
unnamed: U201.2, U202.5
unnamed: U201.3, U202.4
unnamed: U202.2, U203.5
unnamed: U202.3, U203.4
unnamed: U203.2, U204.5
unnamed: U203.3, U204.4
unnamed: U204.2, U205.5
unnamed: U204.3, U205.4
unnamed: U205.2, U206.5
unnamed: U205.3, U206.4
unnamed: U206.2, U207.5
unnamed: U206.3, U207.4
unnamed: U207.2, U208.5
unnamed: U207.3, U208.4
unnamed: U209.2, U210.5
unnamed: U209.3, U210.4
unnamed: U210.2, U211.5
unnamed: U210.3, U211.4
unnamed: U211.2, U212.5
unnamed: U211.3, U212.4
unnamed: U212.2, U213.5
unnamed: U212.3, U213.4
unnamed: U213.2, U214.5
unnamed: U213.3, U214.4
unnamed: U214.2, U215.5
unnamed: U214.3, U215.4
unnamed: U215.2, U216.5
unnamed: U215.3, U216.4
unnamed: U216.2, U217.5
unnamed: U216.3, U217.4
unnamed: U217.2, U218.5
unnamed: U217.3, U218.4
unnamed: U218.2, U219.5
unnamed: U218.3, U219.4
unnamed: U219.2, U220.5
unnamed: U219.3, U220.4
unnamed: U220.2, U221.5
unnamed: U220.3, U221.4
unnamed: U221.2, U222.5
unnamed: U221.3, U222.4
unnamed: U222.2, U223.5
unnamed: U222.3, U223.4
unnamed: U223.2, U224.5
unnamed: U223.3, U224.4
unnamed: U225.2, U226.5
unnamed: U225.3, U226.4
unnamed: U226.2, U227.5
unnamed: U226.3, U227.4
unnamed: U227.2, U228.5
unnamed: U227.3, U228.4
unnamed: U228.2, U229.5
unnamed: U228.3, U229.4
unnamed: U229.2, U230.5
unnamed: U229.3, U230.4
unnamed: U230.2, U231.5
unnamed: U230.3, U231.4
unnamed: U231.2, U232.5
unnamed: U231.3, U232.4
unnamed: U232.2, U233.5
unnamed: U232.3, U233.4
unnamed: U233.2, U234.5
unnamed: U233.3, U234.4
unnamed: U234.2, U235.5
unnamed: U234.3, U235.4
unnamed: U235.2, U236.5
unnamed: U235.3, U236.4
unnamed: U236.2, U237.5
unnamed: U236.3, U237.4
unnamed: U237.2, U238.5
unnamed: U237.3, U238.4
unnamed: U238.2, U239.5
unnamed: U238.3, U239.4
unnamed: U239.2, U240.5
unnamed: U239.3, U240.4
unnamed: U241.2, U242.5
unnamed: U241.3, U242.4
unnamed: U242.2, U243.5
unnamed: U242.3, U243.4
unnamed: U243.2, U244.5
unnamed: U243.3, U244.4
unnamed: U244.2, U245.5
unnamed: U244.3, U245.4
unnamed: U245.2, U246.5
unnamed: U245.3, U246.4
unnamed: U246.2, U247.5
unnamed: U246.3, U247.4
unnamed: U247.2, U248.5
unnamed: U247.3, U248.4
unnamed: U248.2, U249.5
unnamed: U248.3, U249.4
unnamed: U249.2, U250.5
unnamed: U249.3, U250.4
unnamed: U250.2, U251.5
unnamed: U250.3, U251.4
unnamed: U251.2, U252.5
unnamed: U251.3, U252.4
unnamed: U252.2, U253.5
unnamed: U252.3, U253.4
unnamed: U253.2, U254.5
unnamed: U253.3, U254.4
unnamed: U254.2, U255.5
unnamed: U254.3, U255.4
unnamed: U255.2, U256.5
unnamed: U255.3, U256.4
SD1: U16.3, U17.4
SD2: U32.3, U33.4
SD3: U48.3, U49.4
SD4: U64.3, U65.4
SD5: U80.3, U81.4
SD6: U96.3, U97.4
SD7: U112.3, U113.4
SD8: U128.3, U129.4
SD9: U144.3, U145.4
SD10: U160.3, U161.4
SD11: U176.3, U177.4
SD12: U192.3, U193.4
SD13: U208.3, U209.4
SD14: U224.3, U225.4
SD15: U240.3, U241.4
SDS: P1.3, U1.4

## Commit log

2020-12-26 added STLs and firmware
2020-12-28 added python script
